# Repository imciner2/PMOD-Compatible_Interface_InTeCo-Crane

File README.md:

View this project on [CADLAB.io](https://cadlab.io/project/1718). 

# PMOD-Compatible_InTeCo-Interface
PMOD Compatible interface for the 40-pin InTeCo digital connector

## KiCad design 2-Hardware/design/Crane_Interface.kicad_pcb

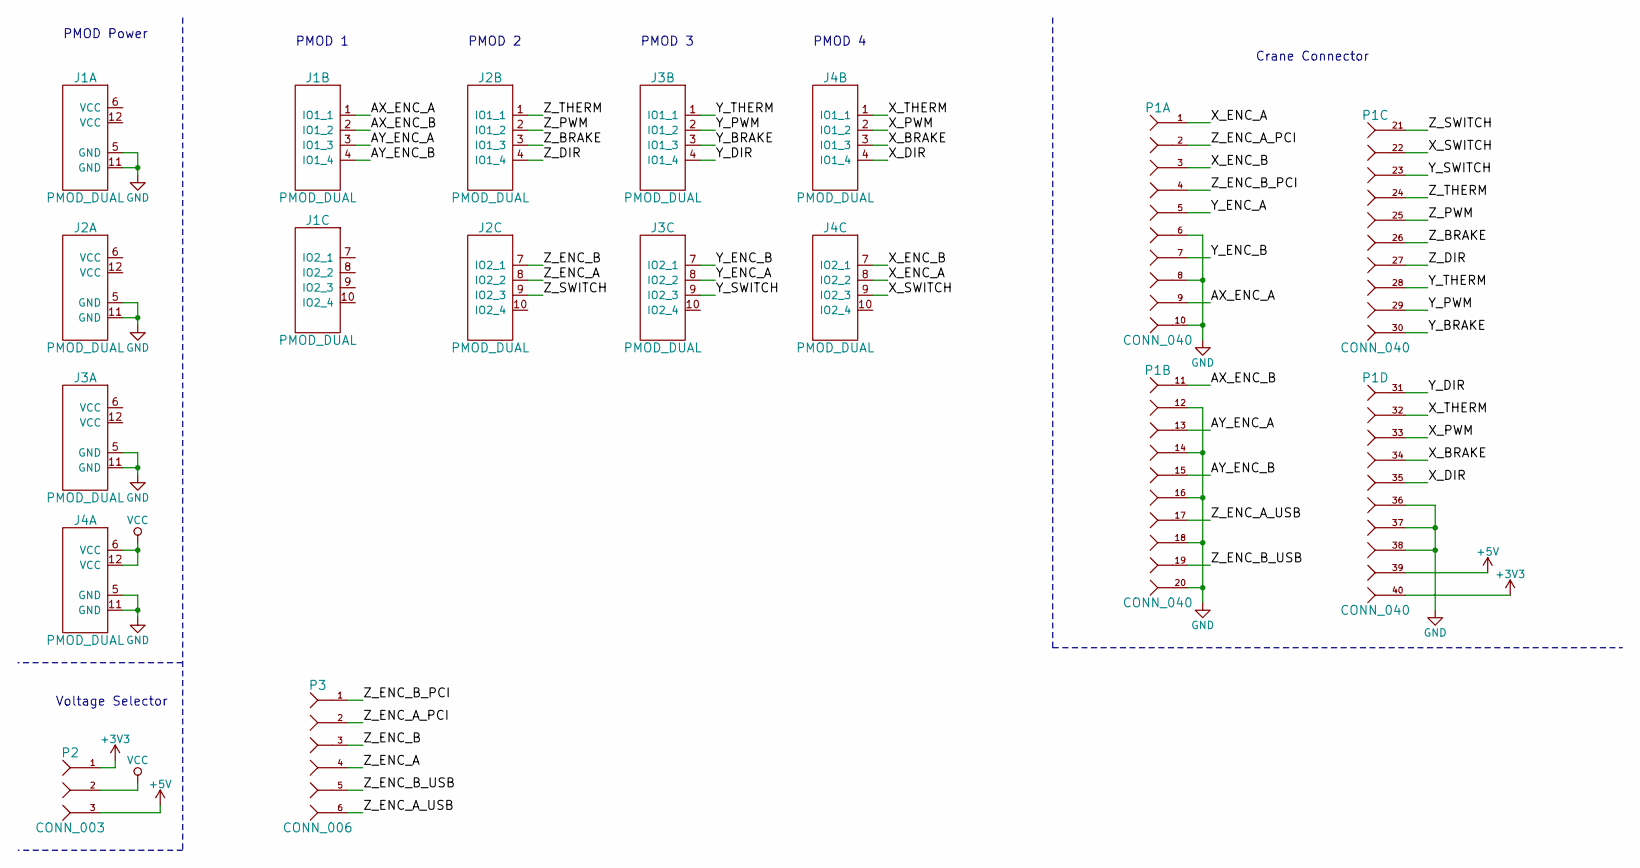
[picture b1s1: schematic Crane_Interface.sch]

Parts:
J1, J2, J3, J4: PMOD_DUAL; PMOD_DOUBLE_MALE
P1: CONN_040; CONN_2.54mm_2x20
P2: CONN_003; CONN_2.54mm_1x03
P3: CONN_006; CONN_2.54mm_2x03

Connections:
+3V3: P1.40, P2.1
+5V: P1.39, P2.3
/AX_ENC_A: J1.1 (IO1_1), P1.9
/AX_ENC_B: J1.2 (IO1_2), P1.11
/AY_ENC_A: J1.3 (IO1_3), P1.13
/AY_ENC_B: J1.4 (IO1_4), P1.15
/X_BRAKE: J4.3 (IO1_3), P1.34
/X_DIR: J4.4 (IO1_4), P1.35
/X_ENC_A: J4.8 (IO2_2), P1.1
/X_ENC_B: J4.7 (IO2_1), P1.3
/X_PWM: J4.2 (IO1_2), P1.33
/X_SWITCH: J4.9 (IO2_3), P1.22
/X_THERM: J4.1 (IO1_1), P1.32
/Y_BRAKE: J3.3 (IO1_3), P1.30
/Y_DIR: J3.4 (IO1_4), P1.31
/Y_ENC_A: J3.8 (IO2_2), P1.5
/Y_ENC_B: J3.7 (IO2_1), P1.7
/Y_PWM: J3.2 (IO1_2), P1.29
/Y_SWITCH: J3.9 (IO2_3), P1.23
/Y_THERM: J3.1 (IO1_1), P1.28
/Z_BRAKE: J2.3 (IO1_3), P1.26
/Z_DIR: J2.4 (IO1_4), P1.27
/Z_ENC_A: J2.8 (IO2_2), P3.4
/Z_ENC_A_PCI: P1.2, P3.2
/Z_ENC_A_USB: P1.17, P3.6
/Z_ENC_B: J2.7 (IO2_1), P3.3
/Z_ENC_B_PCI: P1.4, P3.1
/Z_ENC_B_USB: P1.19, P3.5
/Z_PWM: J2.2 (IO1_2), P1.25
/Z_SWITCH: J2.9 (IO2_3), P1.21
/Z_THERM: J2.1 (IO1_1), P1.24
GND: J1.5 (GND), J1.11 (GND), J2.5 (GND), J2.11 (GND), J3.5 (GND), J3.11 (GND), J4.5 (GND), J4.11 (GND), P1.6, P1.8, P1.10, P1.12, P1.14, P1.16, P1.18, P1.20, P1.36, P1.37, P1.38
VCC: J4.6 (VCC), J4.12 (VCC), P2.2

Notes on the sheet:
Crane Connector
PMOD Power
PMOD 1
PMOD 2
PMOD 3
PMOD 4
Voltage Selector

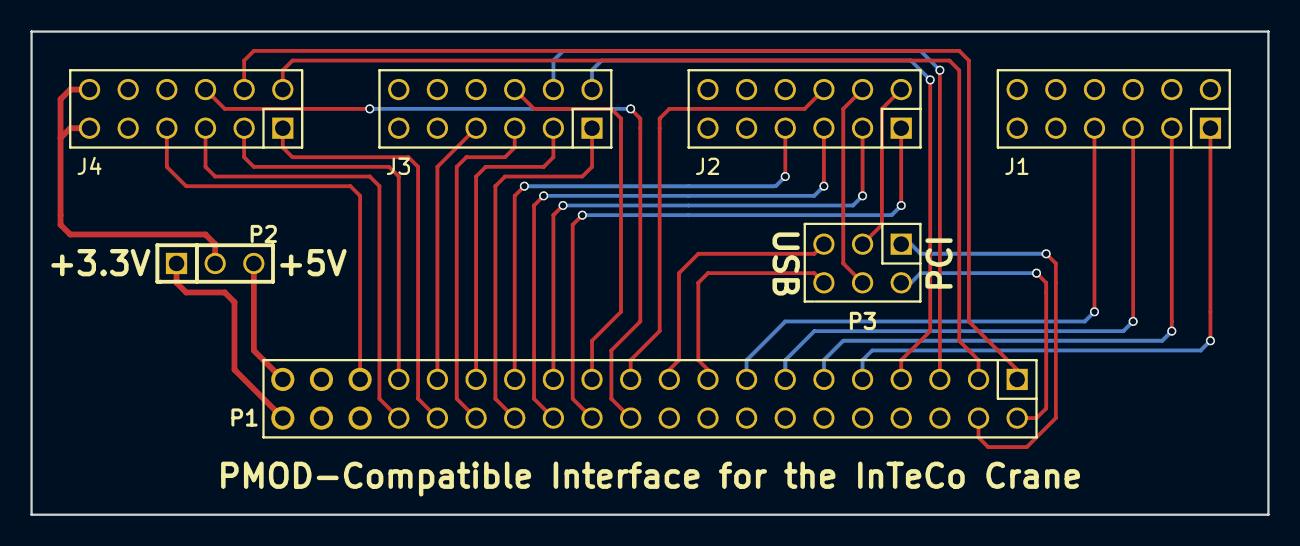
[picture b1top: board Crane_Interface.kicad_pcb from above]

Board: 2 copper layers, 81.3 x 31.8 mm, 7 parts (0 on the bottom side), 33 nets.

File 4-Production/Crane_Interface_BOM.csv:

Source:,/home/im1716/Documents/Electronics/Projects/PMOD-Compatible_Interface_InTeCo-Crane/2-Hardware/design/Crane_Interface.sch,,,,,,,,
Date:,Fri 05 Oct 2018 16:28:31 BST,,,,,,,,
Tool:,Eeschema 4.0.2+dfsg1-stable,,,,,,,,
Generator:,/home/im1716/Documents/Electronics/KiCad-Libraries/BOM_Scripts/bom_csv_grouped_by_value.py,,,,,,,,
Component Count:,7,,,,,,,,
,,,,,,,,,
Item,Qty,Reference(s),Value,LibPart,Footprint,Datasheet,DigikeyNumber,ManufacturerName,ManufacturerNumber
1,4,"J1, J2, J3, J4",PMOD_DUAL,PMOD:PMOD_DUAL,Digilent:PMOD_DOUBLE_MALE,,732-5354-ND,Wurth Electronics Inc.,61301221021
2,1,P1,CONN_040,Connectors:CONN_040,Connectors:CONN_2.54mm_2x20,,S9175-ND,Sullins Connector Solutions,SBH11-PBPC-D20-ST-BK
3,1,P2,CONN_003,Connectors:CONN_003,Connectors:CONN_2.54mm_1x03,,732-5316-ND,Wurth Electronics,61300311121
4,1,P3,CONN_006,Connectors:CONN_006,Connectors:CONN_2.54mm_2x03,,609-3234-ND,Amphenol FCI,67997-206HLF
5,4,,CABLE,,,,1286-1102-ND,Digilent Inc.,240-021-2
6,3,,JUMPERS,,,,S9337-ND,Sullins Connector Solutions,QPC02SXGN-RC

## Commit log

2018-08-21 Added libraries
2018-10-02 Initial schematic work
2018-10-03 Initial design
    * Renamed design
    * Initial schematic and board layout
2018-10-03 Board design
2018-10-03 Datasheets for the connector
2018-10-05 Added silkscreen label
2018-10-17 Production files
2018-12-11 Added Zedboard picture
2018-12-11 Boad render
2018-12-11 Board top view
2018-12-11 Cropped pic
2019-01-08 AXI motor driver modul
2019-01-08 Pin constraints for the Zedboard
2019-01-08 gitignore for Xilinx files
2019-01-08 Test project for the Zedboard
2019-01-09 Updated motor IP cores
    * Added new IP core without AXI
    * Updated metadata for AXI core
2019-01-09 Added drvier files
2019-01-09 Tested motor driver core
2019-01-09 Exported test project to SDK
2019-01-09 first test
2019-01-10 Cleaned up git
2019-01-10 Added register map
2019-01-14 Motor driven using buttons
2019-01-14 Fixed indents
2019-01-14 Fixed more indents
2019-01-17 Interface images for motor driver core
2019-04-27 Backlink to CADLAB.io has been added.
